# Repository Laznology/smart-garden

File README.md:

# Proyek Smart Garden

## Ikhtisar

Smart Garden adalah sistem pertanian cerdas yang memanfaatkan teknologi AI untuk mengoptimalkan pertumbuhan tanaman, penggunaan sumber daya, dan pengelolaan pertanian secara keseluruhan. Sistem ini mengumpulkan data dari berbagai sensor, memprosesnya melalui agen AI, dan memberikan wawasan serta kontrol otomatis untuk pengelolaan kebun yang efisien.

## Struktur Proyek

Proyek ini terbagi menjadi beberapa komponen utama:

1. **Agen AI**: Sistem cerdas untuk analisis data dan pengambilan keputusan
2. **Sensor**: Komponen perangkat keras untuk mengumpulkan data environtmenr dan tanaman
3. **Integrated IoT & AI**: Sistem untuk mentransmisikan data dari sensor ke AI
4. **Pengembangan Hardware**: Desain PCB 

## Struktur Folder

```
smart-garden/
├── ai-agent/               # Codebase AI Agent
├── sensors/                # Codebase Microcontroller 
├── docs/                   # Dokumentasi proyek
└── pcb/                    # Desain PCB dan skematik

```

## Hall of Fame

### AI Agent

<div align="center">
  <table>
    <tr>
      <td align="center">
        <a href="https://github.com/dhaniil">
          <br>
          <sub><b>Laztech</b></sub>
        </a>
      </td>
      <td align="center">
        <a href="https://github.com/mirekan">
          <br>
          <sub><b>Mirekan</b></sub>
        </a>
      </td>
    </tr>
  </table>
</div>

### IoT Sensor

<div align="center">
  <table>
    <tr>
      <td align="center">
        <a href="https://github.com/HaqZ60">
          <br>
          <sub><b>HaqZ</b></sub>
        </a>
      </td>
      <td align="center">
        <a href="https://github.com/tsabith">
          <br>
          <sub><b>Tsabit</b></sub>
        </a>
      </td>
      <td align="center">
        <a href="https://github.com/vazul76">
          <br>
          <sub><b>Vazul</b></sub>
        </a>
      </td>
    </tr>
  </table>
</div>

### PCB & Hardware

<div align="center">
  <table>
    <tr>
      <td align="center">
        <a href="https://github.com/Eumerandom">
          <br>
          <sub><b>Eumerandom</b></sub>
        </a>
      </td>
      <td align="center">
        <a href="https://github.com/">
          <br>
          <sub><b>sna</b></sub>
        </a>
      </td>
      <td align="center">
        <a href="https://github.com/">
          <br>
          <sub><b>Feyy</b></sub>
        </a>
      </td>
      <td align="center">
        <a href="https://github.com/akbaradhakw">
          <br>
          <sub><b>Akbar asli yang ada K.Wnya</b></sub>
        </a>
      </td>
    </tr>
  </table>
</div>

---

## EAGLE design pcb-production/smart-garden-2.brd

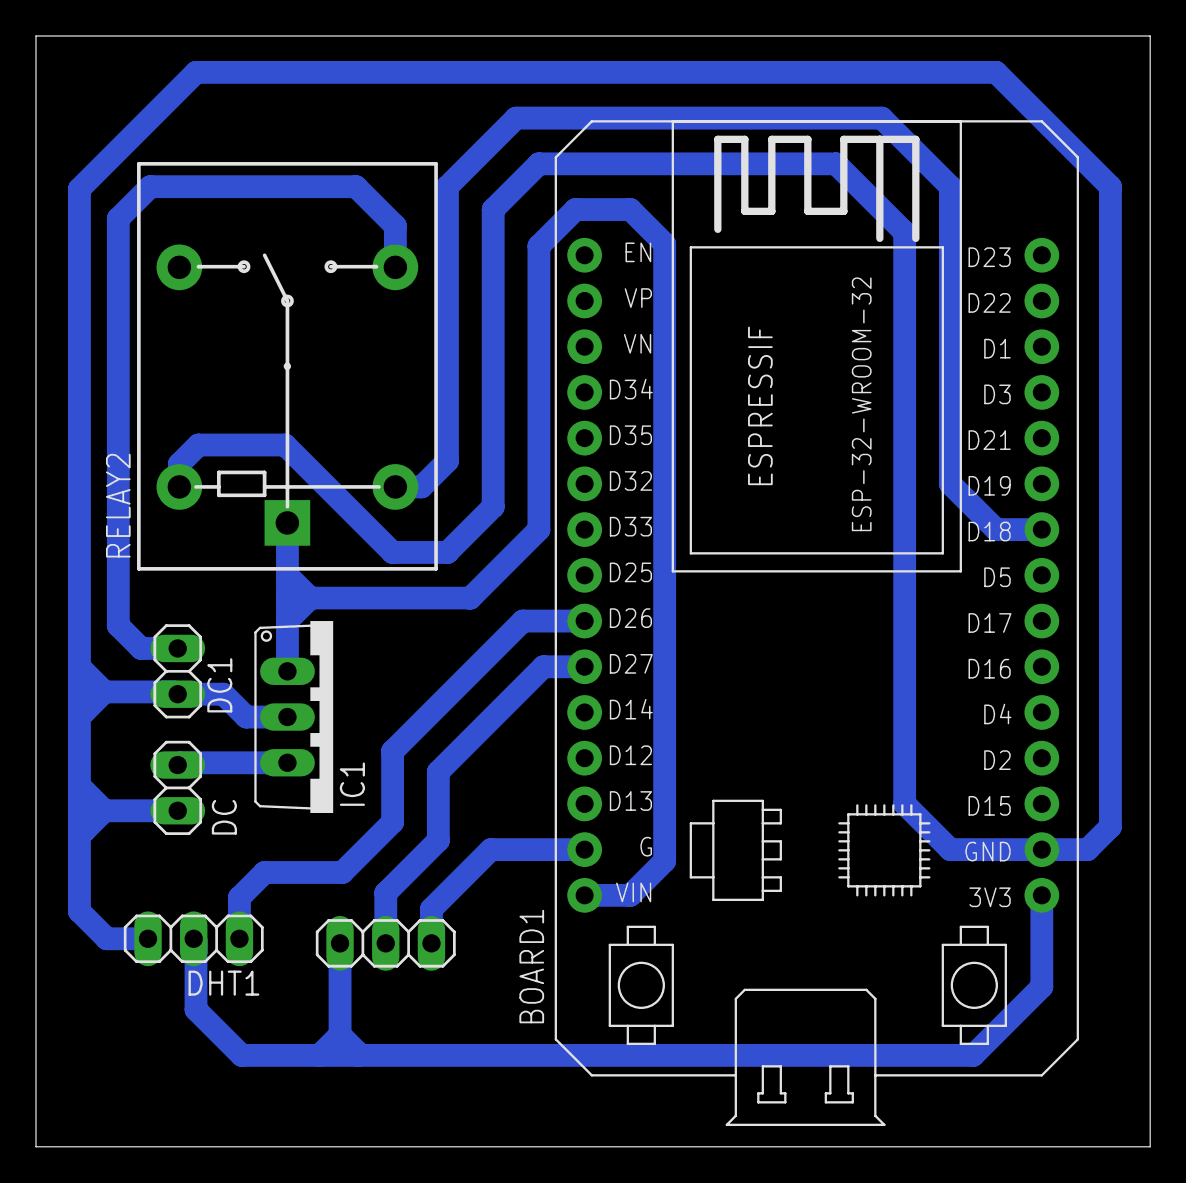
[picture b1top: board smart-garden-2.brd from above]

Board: 2 copper layers, 61.9 x 61.7 mm, 7 parts (0 on the bottom side), 9 nets.

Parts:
BOARD1: ESP32DEVKITV1; ESP32-DEVKITV1
DC, DC1: 1X02
DHT1, DHT22: 1X03
IC1: 7805TV; TO220V
RELAY2: RELAY-SPDT; RELAY_G5LE

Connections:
unnamed: BOARD1.D26, DHT1.1
unnamed: BOARD1.D27, DHT22.2
unnamed: BOARD1.3V3, DHT1.2, DHT22.1
unnamed: BOARD1.D18, RELAY2.2
unnamed: BOARD1.VIN, IC1.1, RELAY2.1
unnamed: BOARD1.GND, DHT22.3
unnamed: DC1.1, RELAY2.3
unnamed: DC.1, IC1.3
unnamed: BOARD1.GND@1, DC.2, DC1.2, DHT1.3, IC1.2, RELAY2.5

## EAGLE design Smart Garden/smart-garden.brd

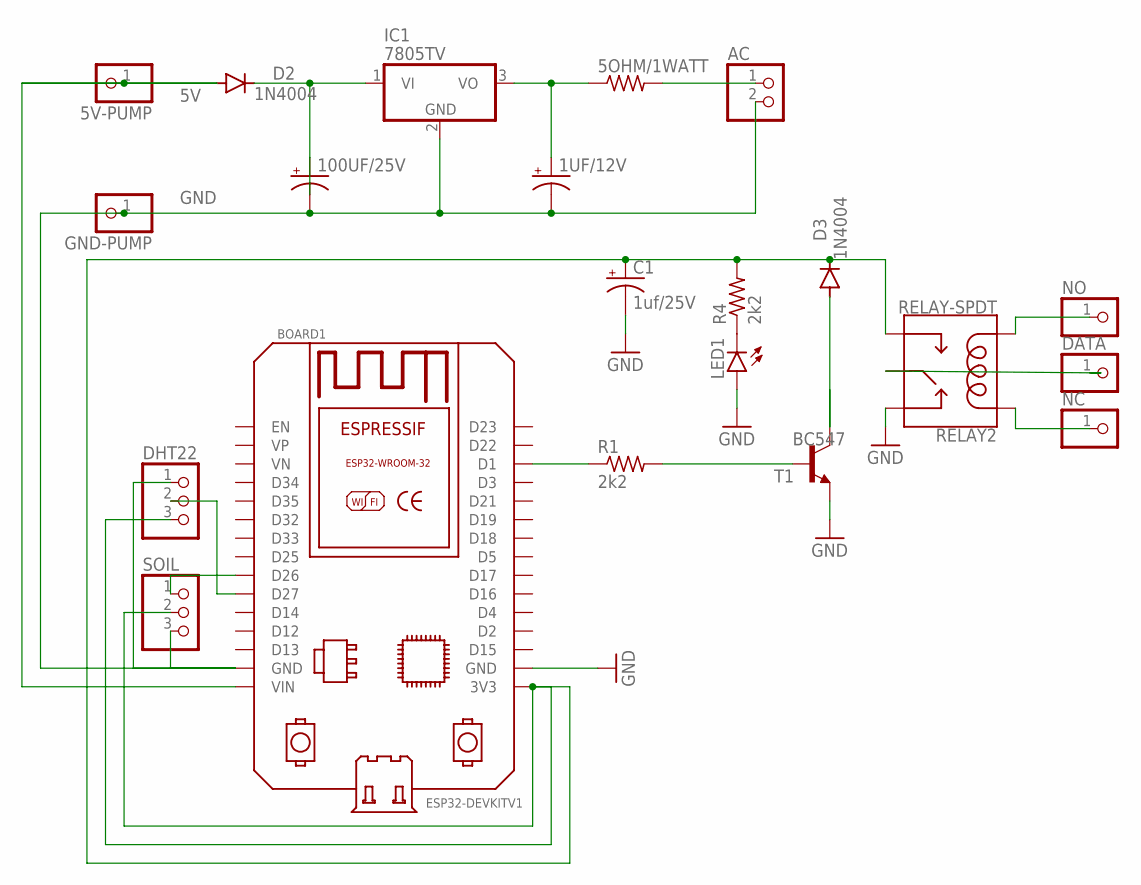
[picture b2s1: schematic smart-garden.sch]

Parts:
1UF/12V, 100UF/25V: CPOL-USE3.5-10; E3,5-10
5OHM/1WATT: R-US_0309/12; 0309/12
5V-PUMP: PINHD-1X1; 1X01
AC: PINHD-1X2; 1X02
BOARD1: ESP32DEVKITV1; ESP32-DEVKITV1
C1: 1uf/25V; E3,5-10
D2, D3: 1N4004; DO41-10
DATA: PINHD-1X1; 1X01
DHT22: PINHD-1X3; 1X03
GND-PUMP: PINHD-1X1; 1X01
IC1: 7805TV; TO220V
LED1: LED5MM
NC: PINHD-1X1; 1X01
NO: PINHD-1X1; 1X01
R1, R4: 2k2; 0309/12
RELAY2: RELAY-SPDT; RELAY_G5LE
SOIL: PINHD-1X3; 1X03
T1: BC547; TO92-CBE

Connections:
5V: 5V-PUMP.1, BOARD1.VIN, D2.A
GND: 1UF/12V.-, 100UF/25V.-, AC.2, BOARD1.GND@1 (GND), C1.-, GND-PUMP.1, IC1.2 (GND), LED1.A, RELAY2.4 (NC), T1.E
unnamed: BOARD1.D26, SOIL.1
unnamed: BOARD1.D27, DHT22.2
unnamed: BOARD1.GND, DHT22.1, SOIL.3
unnamed: LED1.K (C), R4.1
unnamed: BOARD1.D1, R1.1
unnamed: BOARD1.3V3, C1.+, D3.C, DHT22.3, R4.2, RELAY2.3 (NO), SOIL.2
unnamed: 100UF/25V.+, D2.C, IC1.1 (VI)
unnamed: 1UF/12V.+, 5OHM/1WATT.1, IC1.3 (VO)
unnamed: 5OHM/1WATT.2, AC.1
unnamed: R1.2, T1.B
unnamed: D3.A, T1.C
unnamed: NC.1, RELAY2.2 (COIL1)
unnamed: DATA.1, RELAY2.1 (MAIN)
unnamed: NO.1, RELAY2.5 (COIL2)

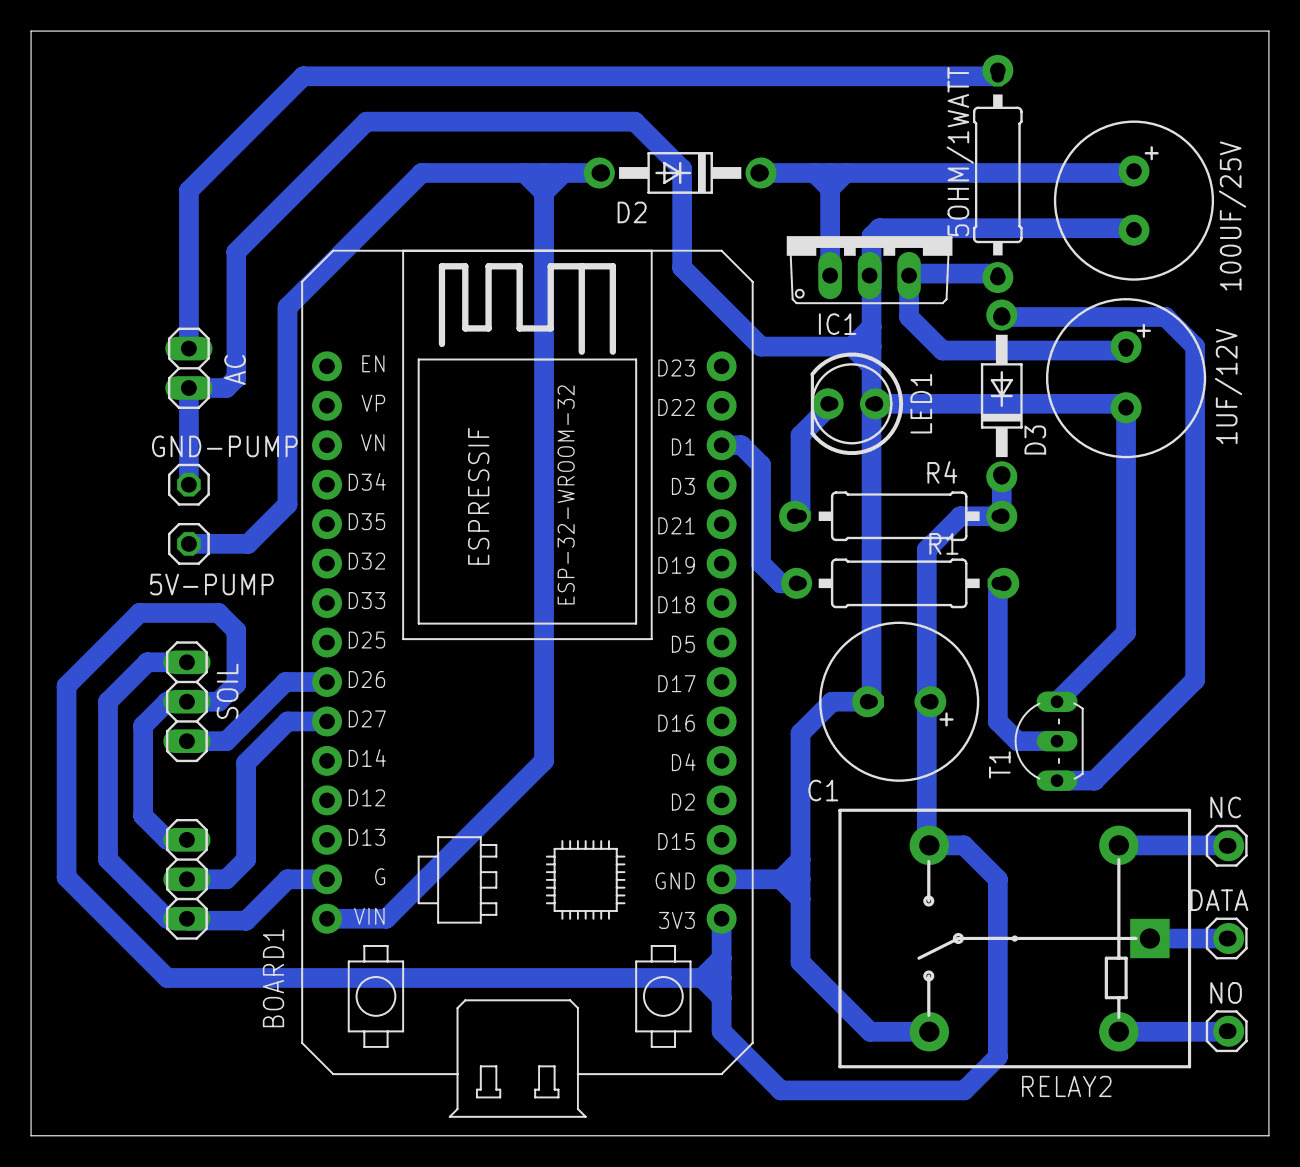
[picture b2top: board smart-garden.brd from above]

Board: 2 copper layers, 79.7 x 71.1 mm, 21 parts (0 on the bottom side), 16 nets.

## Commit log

2025-04-16 Readme.md
2025-04-16 Startup AI Agent
2025-04-16 Remove README.md
2025-04-16 Inisiasi Codebase AI
2025-04-17 [Progress] Kecil-Kecilan
2025-04-18 Add/Prisma Model
    feat(schema): define SensorReading, Analytic, Message, and Topic models with relationships and indexing
2025-04-18 Add/mqtt reading
    feat(controller): add mqtt client service and config for sensor readings
2025-04-18 [Progress] Telegram
2025-04-18 Add/Prisma Model
    feat(schema): added Farm Model and relation to sensor reading
2025-04-18 Change/Prisma Model
    feat(schema): Change sensor reading value type to json
2025-04-18 [Finished] PCB
    Kalo mau download bisa yang board aja (.brd) atau board+schematic (.sch), kalo cuma download schematicnya aja nanti boardnya reset
2025-04-18 [Update] Agent
2025-04-18 [Refactor] Handle Message
2025-04-18 [Refactor] Handle Message yang lebih unipersal, pwehh
2025-04-19 chore(schema): changing many things on the analytics table and adjusment to the sensor_readings table
    Analytics table added min max mean, also added started date and end date for indexing. For the sensor_readings changing value datatype to float for better accuracy
2025-04-19 🚧 AI blm selesai
2025-04-19 AI sudah konek
2025-04-20 AI Data Injection
2025-04-20 feat(mqtt): added dynamic topic name for sensor and create 2 records every readings
    not yet tested and still cant used before creating method for admin topic Controllers MQTT
2025-04-21 feat(mqtt): Added MQTT Dynamic Topic Controller for sensor and inserting to database on table topics
2025-04-23 Progress
2025-04-24 Mbuh Lah
2025-04-24 Done
2025-04-24 committed
2025-04-24 feat(mqtt): update MQTT Service
    update for dynamic mqtt controller
2025-04-25 Refactor to single entry point
    change telegram to class instance from old function
2025-04-25 added .env.example
2025-04-25 Inject Robust Data
2025-04-26 Ready To Test
2025-04-26 'Merapikan'
2025-04-26 [Release] 1.0.0
2025-04-28 [Update] Remake PCB
2025-06-11 code
2025-06-12 [Refactor] Update bot commands and MQTT handling; remove unused commands and improve topic management
2025-06-12 [Refactor] Enhance sensor reading handling and database interactions; support multiple readings and improve error handling
2025-06-13 [Refactor] Update Prisma schema to change farmId type to String; enhance MQTT message handling and processing for sensor readings
2025-06-15 [Refactor] Remove unused files and clean up the project structure
2025-06-15 [Feat] Add n8n workflow
2025-06-16 [Refactor] Update n8n workflow
2025-06-16 [Refactor] Update AI Agent parameters and enhance Telegram integration in n8n workflow

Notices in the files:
parts and their libraries:
SparkFun-Electromechanical: Licensing: Creative Commons ShareAlike 4.0 International - https://creativecommons.org/licenses/by-sa/4.0
